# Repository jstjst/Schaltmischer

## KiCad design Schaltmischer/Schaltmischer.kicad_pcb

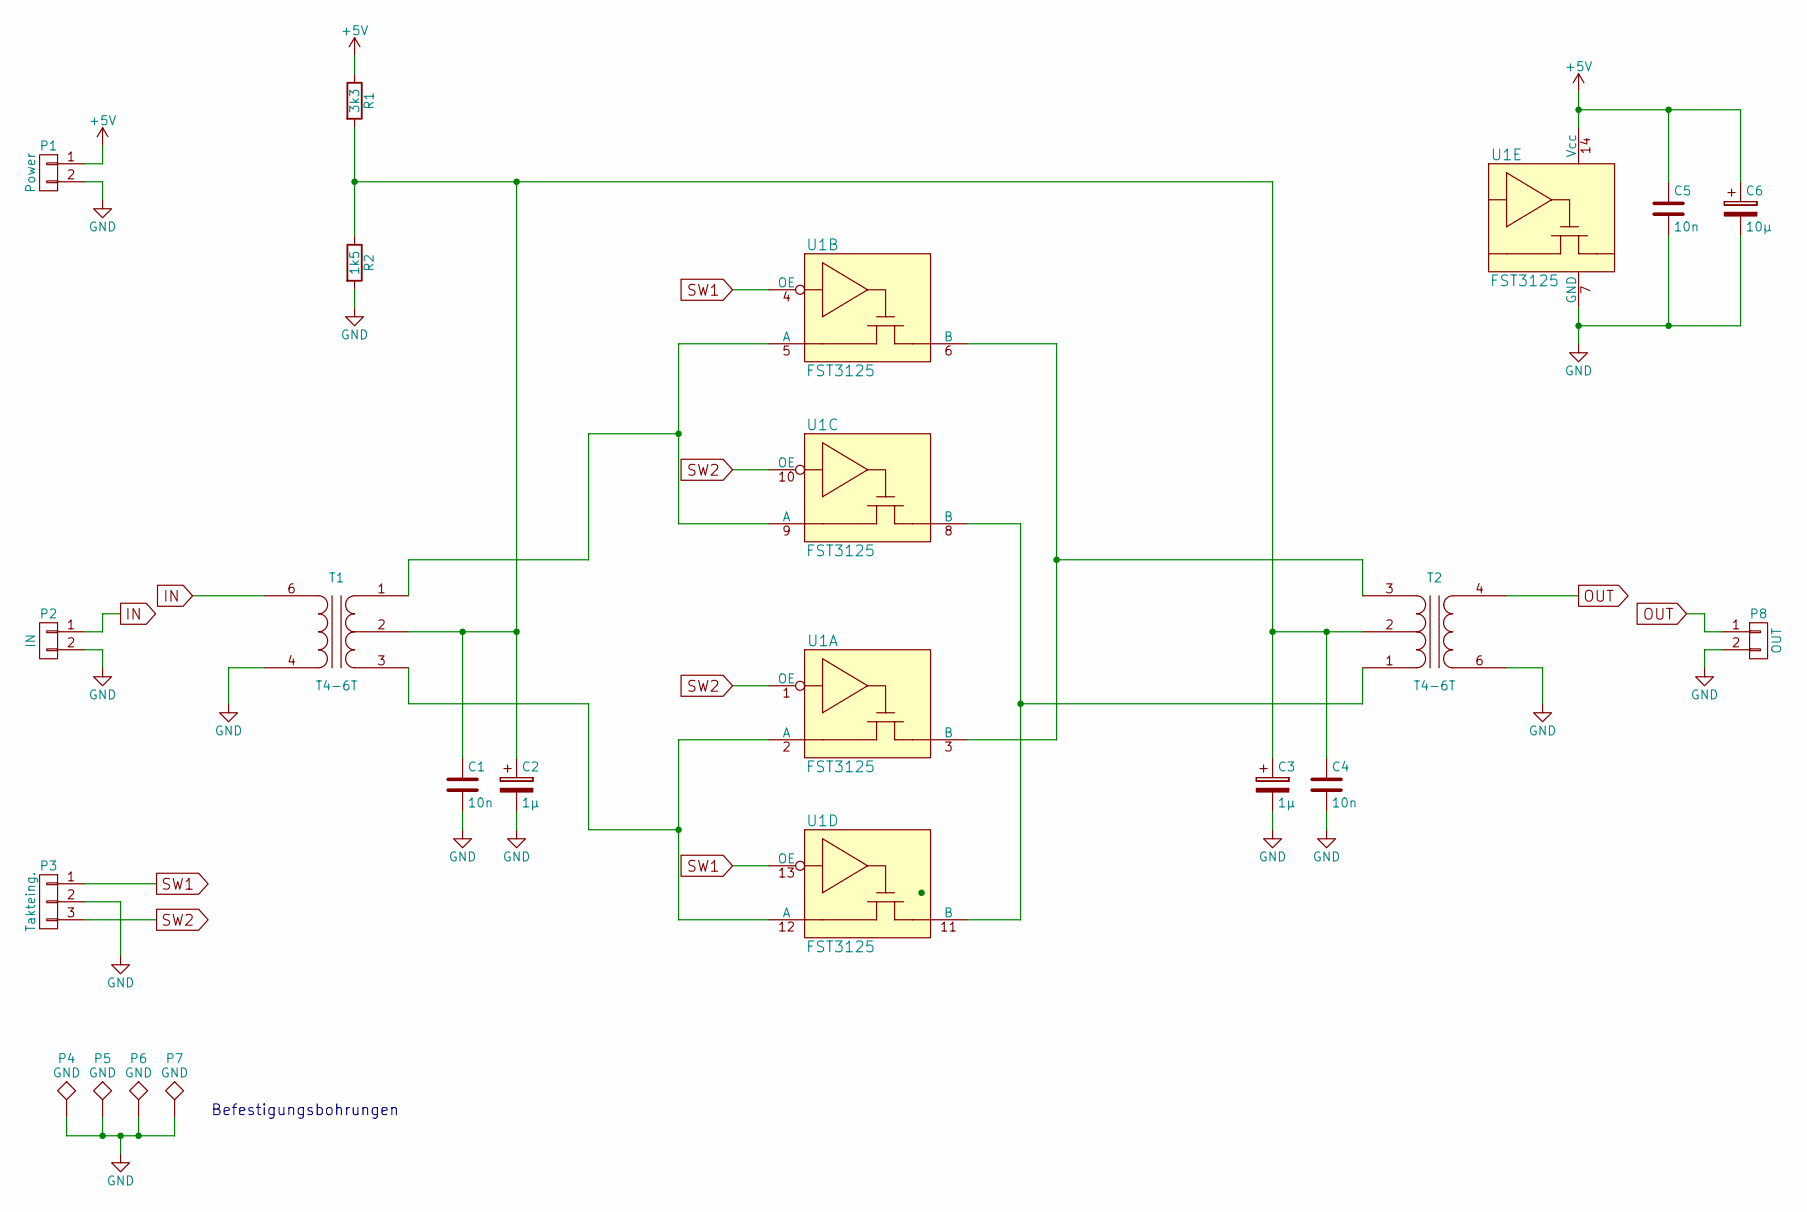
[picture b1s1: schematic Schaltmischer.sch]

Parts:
C1, C4, C5: 10n; C_1206_HandSoldering
C2, C3: 1µ; C_1206_HandSoldering
C6: 10µ; C_1206_HandSoldering
P1: Power; Pin_Header_Straight_1x02_Pitch2.54mm
P2: IN; Pin_Header_Straight_1x02_Pitch2.54mm
P3: Takteing.; Pin_Header_Straight_1x03_Pitch2.54mm
P4, P5, P6, P7: GND; MountingHole_3.2mm_M3_Pad_Via
P8: OUT; Pin_Header_Straight_1x02_Pitch2.54mm
R1: 3k3; R_1206_HandSoldering
R2: 1k5; R_1206_HandSoldering
T1, T2: T4-6T; T-622
U1: FST3125; SOIC-14_3.9x8.7mm_Pitch1.27mm

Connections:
+5V: C5.1, C6.1, P1.1, R1.1, U1.14 (Vcc)
GND: C1.2, C2.2, C3.2, C4.2, C5.2, C6.2, P1.2, P2.2, P3.2, P4.1, P5.1, P6.1, P7.1, P8.2, R2.2, T1.4 (S1), T2.6 (S2), U1.7 (GND)
IN: P2.1, T1.6 (S2)
unnamed: C1.1, C2.1, C3.1, C4.1, R1.2, R2.1, T1.2 (PM), T2.2 (PM)
unnamed: T1.1 (PR1), U1.5 (A), U1.9 (A)
unnamed: T1.3 (PR2), U1.2 (A), U1.12 (A)
unnamed: T2.1 (PR1), U1.8 (B), U1.11 (B)
unnamed: T2.3 (PR2), U1.3 (B), U1.6 (B)
OUT: P8.1, T2.4 (S1)
SW1: P3.1, U1.4 (OE), U1.13 (OE)
SW2: P3.3, U1.1 (OE), U1.10 (OE)

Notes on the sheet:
Befestigungsbohrungen

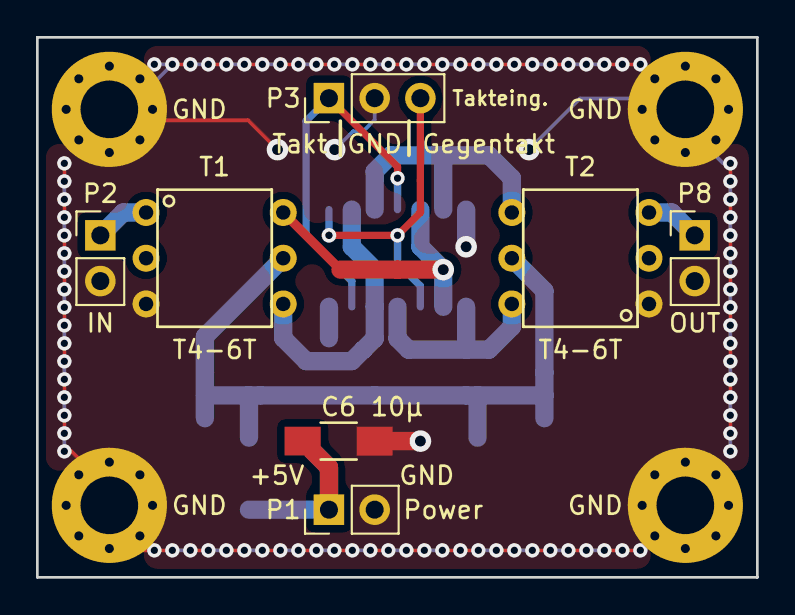
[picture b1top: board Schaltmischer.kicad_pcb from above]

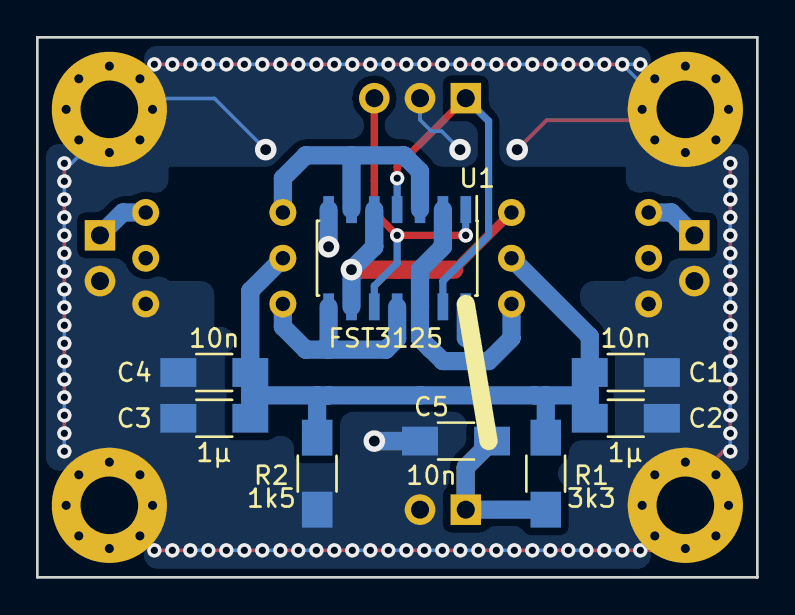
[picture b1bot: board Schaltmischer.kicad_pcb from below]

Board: 2 copper layers, 40.0 x 30.0 mm, 19 parts (8 on the bottom side), 11 nets.

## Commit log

2018-04-14 datasheet
2018-04-14 Schaltplan
2018-04-14 Schaltplan Rev A
2018-04-14 Schaltplan Rev B
2018-04-14 Schaltplan Rev C
2018-04-15 Datenblatt Trafo
2018-04-15 Schaltplan Rev D, Layout Rev A
2018-04-15 save before gnd floating
2018-04-15 save after gnd floating
2018-04-16 Sicherung vor Trafo wechsel im layout
2018-04-16 neues Datanblatt
2018-04-16 Schaltplan Rev E; Layout Rev B
